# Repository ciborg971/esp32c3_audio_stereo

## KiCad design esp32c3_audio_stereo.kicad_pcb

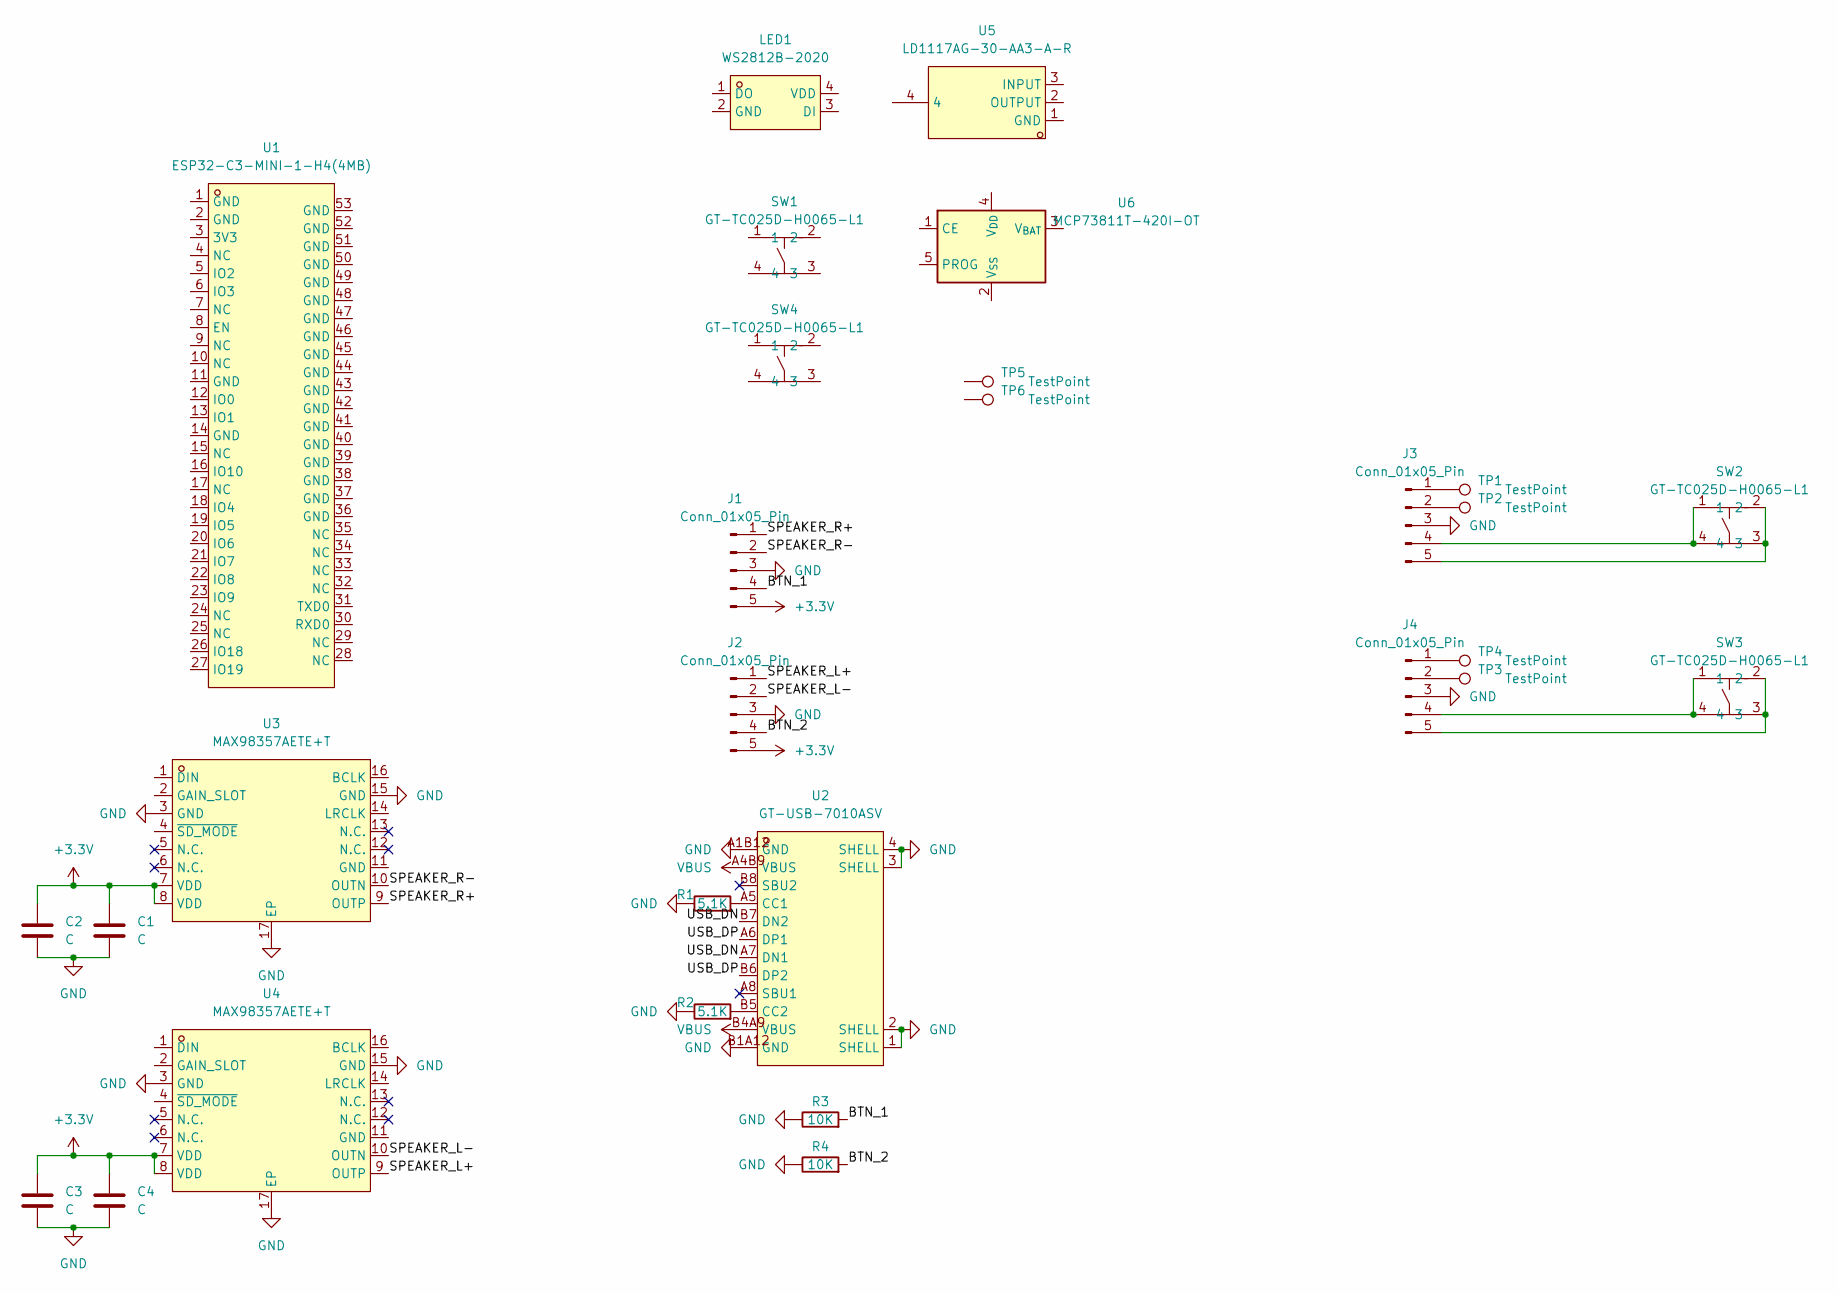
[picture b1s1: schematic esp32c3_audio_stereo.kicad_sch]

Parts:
C1, C2, C3, C4: C; C_0402_1005Metric
J1, J2, J3, J4: Conn_01x05_Pin; JST_SH_SM05B-SRSS-TB_1x05-1MP_P1.00mm_Horizontal
LED1: WS2812B-2020; LED-SMD_4P-L2.0-W2.0-TL_WS2812B-2020; LCSC Part C965555
R1, R2: 5.1K; R_0402_1005Metric
R3, R4: 10K; R_0402_1005Metric
SW1, SW2, SW3, SW4: GT-TC025D-H0065-L1; SW-SMD_4P-L3.0-W2.6-P1.80-LS3.4-TL; LCSC Part C778132
TP1, TP2, TP3, TP4, TP5, TP6: TestPoint; TestPoint_Pad_D1.5mm
U1: ESP32-C3-MINI-1-H4(4MB); WIFIM-SMD_ESP32-C3-MINI-1; LCSC Part C2934569
U2: GT-USB-7010ASV; USB-C-SMD_G-SWITCH_GT-USB-7010ASV; LCSC Part C2988369
U3, U4: MAX98357AETE+T; TQFN-16_L3.0-W3.0-P0.50-BL-EP1.5; LCSC Part C910544
U5: LD1117AG-30-AA3-A-R; SOT-223_L6.5-W3.5-P2.30-LS7.0-BR; LCSC Part C190250
U6: MCP73811T-420I-OT; SOT-23-5

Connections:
+3.3V: C1.1, C2.1, C3.1, C4.1, J1.5, J2.5, U3.7 (VDD), U3.8 (VDD), U4.7 (VDD), U4.8 (VDD)
/BTN_1: J1.4, R3.2
/BTN_2: J2.4, R4.2
/SPEAKER_L+: J2.1, U4.9 (OUTP)
/SPEAKER_L-: J2.2, U4.10 (OUTN)
/SPEAKER_R+: J1.1, U3.9 (OUTP)
/SPEAKER_R-: J1.2, U3.10 (OUTN)
/USB_DN: U2.A7 (DN1), U2.B7 (DN2)
/USB_DP: U2.A6 (DP1), U2.B6 (DP2)
GND: C1.2, C2.2, C3.2, C4.2, J1.3, J2.3, J3.3, J4.3, R1.1, R2.1, R3.1, R4.1, U2.1 (SHELL), U2.2 (SHELL), U2.3 (SHELL), U2.4 (SHELL), U2.A1B12 (GND), U2.B1A12 (GND), U3.3 (GND), U3.15 (GND), U3.17 (EP), U4.3 (GND), U4.15 (GND), U4.17 (EP)
unnamed: J3.1, TP1.1
unnamed: J3.2, TP2.1
unnamed: J3.4, SW2.1, SW2.4
unnamed: J3.5, SW2.2, SW2.3
unnamed: J4.1, TP4.1
unnamed: J4.2, TP3.1
unnamed: J4.4, SW3.1, SW3.4
unnamed: J4.5, SW3.2, SW3.3
unnamed: R1.2, U2.A5 (CC1)
unnamed: R2.2, U2.B5 (CC2)
VBUS: U2.A4B9 (VBUS), U2.B4A9 (VBUS)

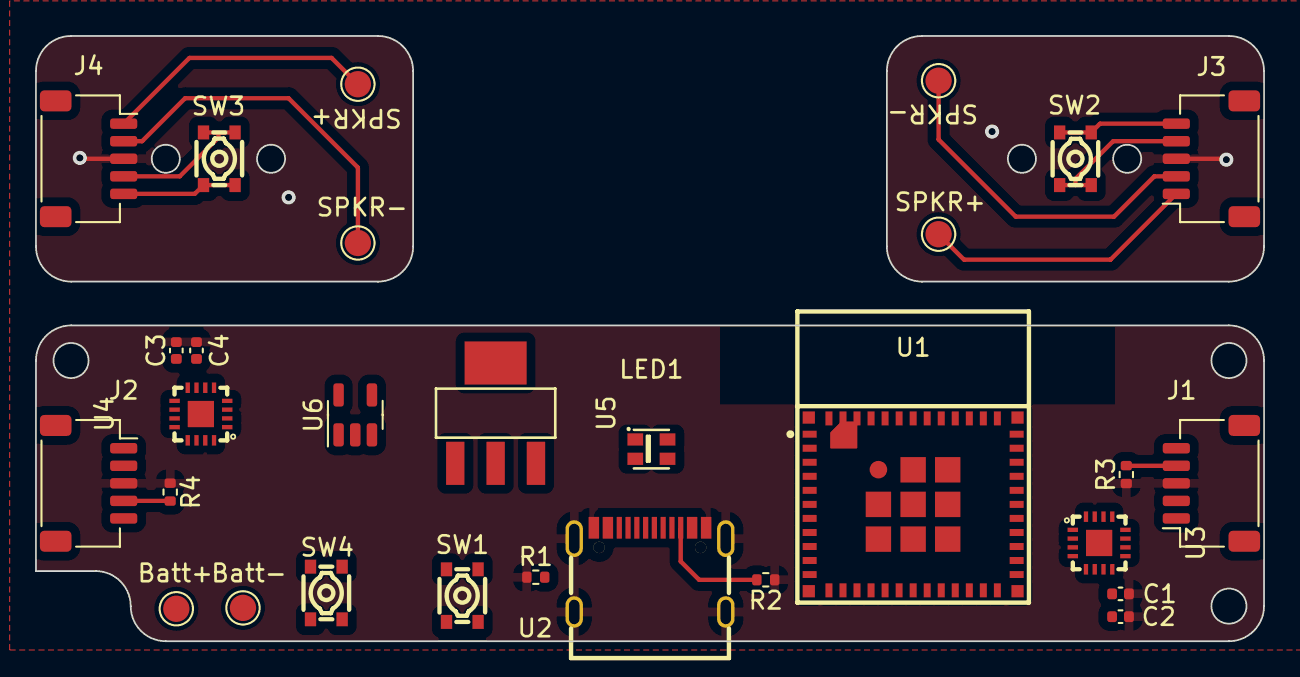
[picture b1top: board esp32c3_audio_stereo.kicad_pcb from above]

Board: 2 copper layers, 70.0 x 34.5 mm, 29 parts (0 on the bottom side), 21 nets.
